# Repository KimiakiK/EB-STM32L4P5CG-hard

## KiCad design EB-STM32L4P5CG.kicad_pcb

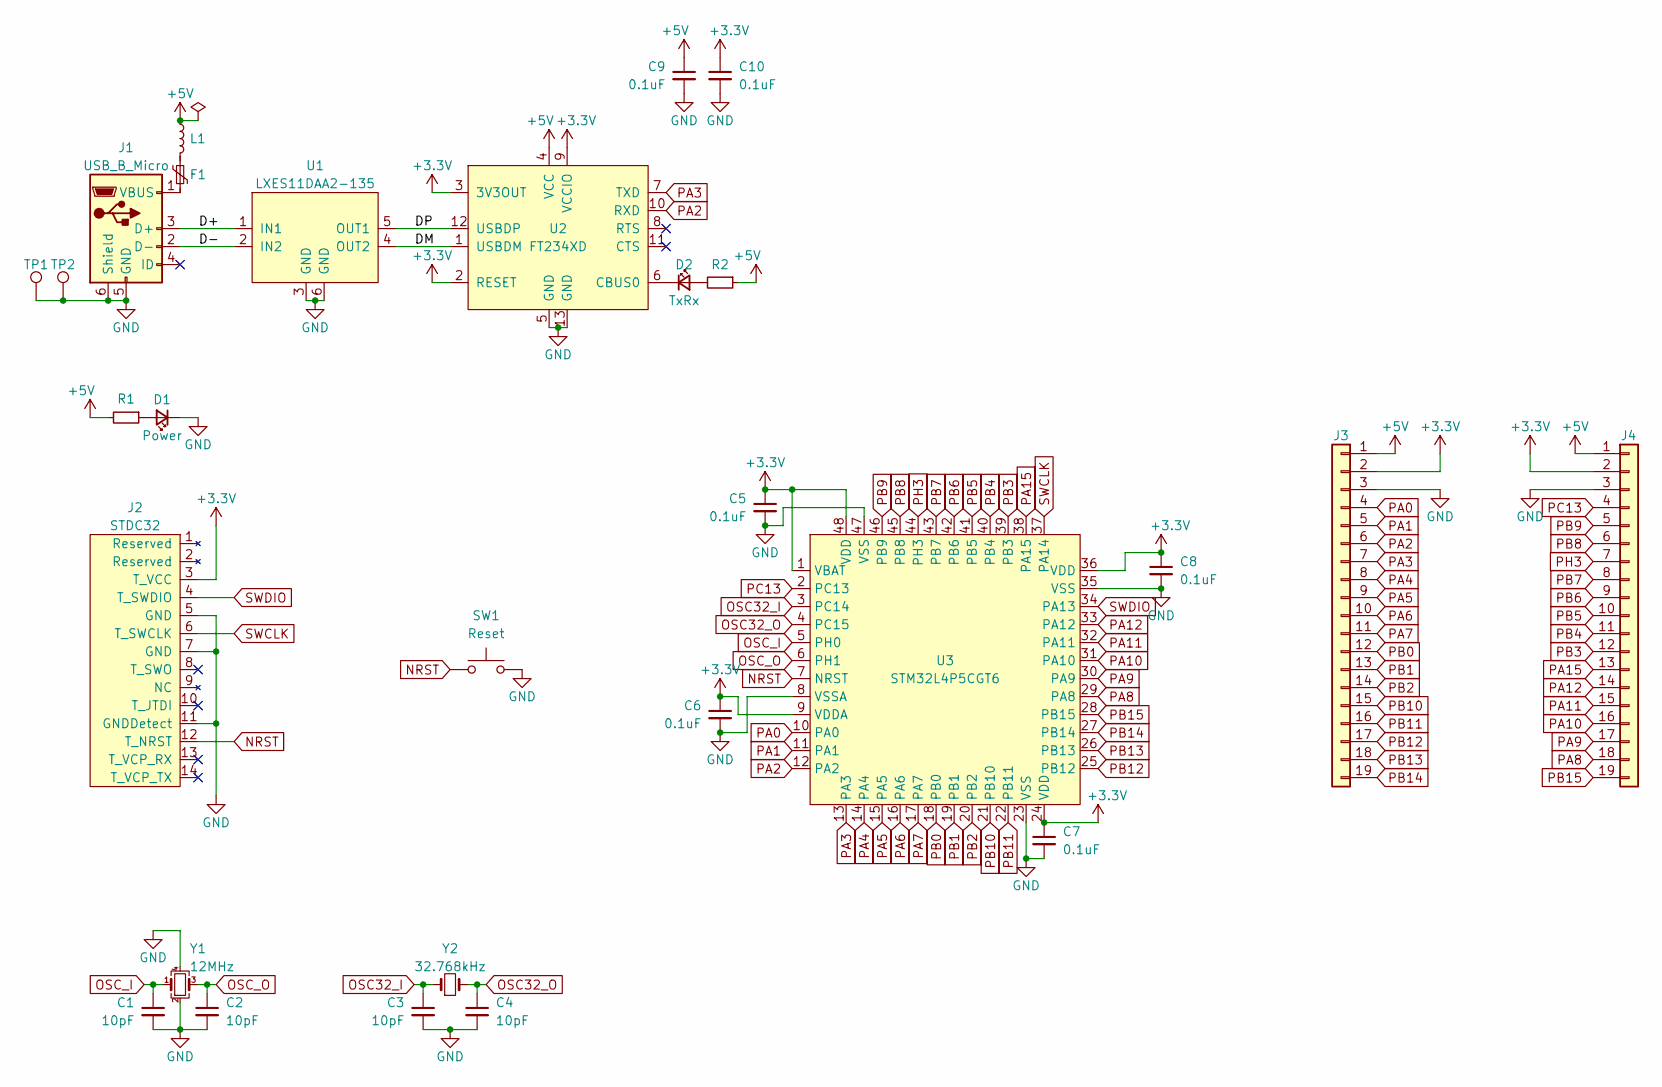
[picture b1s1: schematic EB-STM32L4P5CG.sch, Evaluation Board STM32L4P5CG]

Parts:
C1, C2, C3, C4: 10pF; 1005Metric
C5, C6, C7, C8, C9, C10: 0.1uF; 1608Metric
D1: Power; 1608Metric
D2: TxRx; 1608Metric
F1: ResettableFuse; 1608Metric
J1: USB_B_Micro; ZX62-B-5PA_2
J2: STDC32; BoxHeader_SMD_1.27mm_2x7pin
J3, J4: Conn_01x19; PinHeader_19pin
L1: FerriteBead; 1608Metric
R1, R2: R; 1608Metric
SW1: Reset; SW_TVAF06
TP1, TP2: TestPoint; TestPoint_THTPad_1.6x1.6mm_Drill1.0mm
U1: LXES11DAA2-135; LXES11D
U2: FT234XD; DFN-12-1EP_3x3mm_P0.45mm_EP1.66x2.38mm
U3: STM32L4P5CGT6; LQFP-48_7x7mm_P0.5mm_FusionPCB
Y1: 12MHz; Crystal_SMD_3225-4Pin_3.2x2.5mm_HandSoldering
Y2: 32.768kHz; Crystal_SMD_3215-2Pin

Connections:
+3V3: C5.1, C6.1, C7.1, C8.1, C10.1, J2.3 (T_VCC), J3.2, J4.2, U2.2 (RESET), U2.3 (3V3OUT), U2.9 (VCCIO), U3.1 (VBAT), U3.9 (VDDA), U3.24 (VDD), U3.36 (VDD), U3.48 (VDD)
+5V: C9.1, J3.1, J4.1, L1.1, R1.2, R2.1, U2.4 (VCC)
/D+: J1.3 (D+), U1.1 (IN1)
/D-: J1.2 (D-), U1.2 (IN2)
/DM: U1.4 (OUT2), U2.1 (USBDM)
/DP: U1.5 (OUT1), U2.12 (USBDP)
GND: C1.2, C2.2, C3.2, C4.2, C5.2, C6.2, C7.2, C8.2, C9.2, C10.2, D1.1 (K), J1.5 (GND), J1.6 (Shield), J2.5 (GND), J2.7 (GND), J2.11 (GNDDetect), J3.3, J4.3, SW1.2, TP1.1, TP2.1, U1.3 (GND), U1.6 (GND), U2.5 (GND), U2.13 (GND), U3.8 (VSSA), U3.23 (VSS), U3.35 (VSS), U3.47 (VSS), Y1.2, Y1.4
NRST: J2.12 (T_NRST), SW1.1, U3.7 (NRST)
unnamed: D1.2 (A), R1.1
unnamed: D2.1 (K), U2.6 (CBUS0)
unnamed: D2.2 (A), R2.2
unnamed: F1.1, L1.2
unnamed: F1.2, J1.1 (VBUS)
OSC32_I: C3.1, U3.3 (PC14), Y2.1
OSC32_O: C4.1, U3.4 (PC15), Y2.2
OSC_I: C1.1, U3.5 (PH0), Y1.1
OSC_O: C2.1, U3.6 (PH1), Y1.3
PA0: J3.4, U3.10 (PA0)
PA1: J3.5, U3.11 (PA1)
PA2: J3.6, U2.10 (RXD), U3.12 (PA2)
PA3: J3.7, U2.7 (TXD), U3.13 (PA3)
PA4: J3.8, U3.14 (PA4)
PA5: J3.9, U3.15 (PA5)
PA6: J3.10, U3.16 (PA6)
PA7: J3.11, U3.17 (PA7)
PA8: J4.18, U3.29 (PA8)
PA9: J4.17, U3.30 (PA9)
PA10: J4.16, U3.31 (PA10)
PA11: J4.15, U3.32 (PA11)
PA12: J4.14, U3.33 (PA12)
PA15: J4.13, U3.38 (PA15)
PB0: J3.12, U3.18 (PB0)
PB1: J3.13, U3.19 (PB1)
PB2: J3.14, U3.20 (PB2)
PB3: J4.12, U3.39 (PB3)
PB4: J4.11, U3.40 (PB4)
PB5: J4.10, U3.41 (PB5)
PB6: J4.9, U3.42 (PB6)
PB7: J4.8, U3.43 (PB7)
PB8: J4.6, U3.45 (PB8)
PB9: J4.5, U3.46 (PB9)
PB10: J3.15, U3.21 (PB10)
PB11: J3.16, U3.22 (PB11)
PB12: J3.17, U3.25 (PB12)
PB13: J3.18, U3.26 (PB13)
PB14: J3.19, U3.27 (PB14)
PB15: J4.19, U3.28 (PB15)
PC13: J4.4, U3.2 (PC13)
PH3: J4.7, U3.44 (PH3)
SWCLK: J2.6 (T_SWCLK), U3.37 (PA14)
SWDIO: J2.4 (T_SWDIO), U3.34 (PA13)

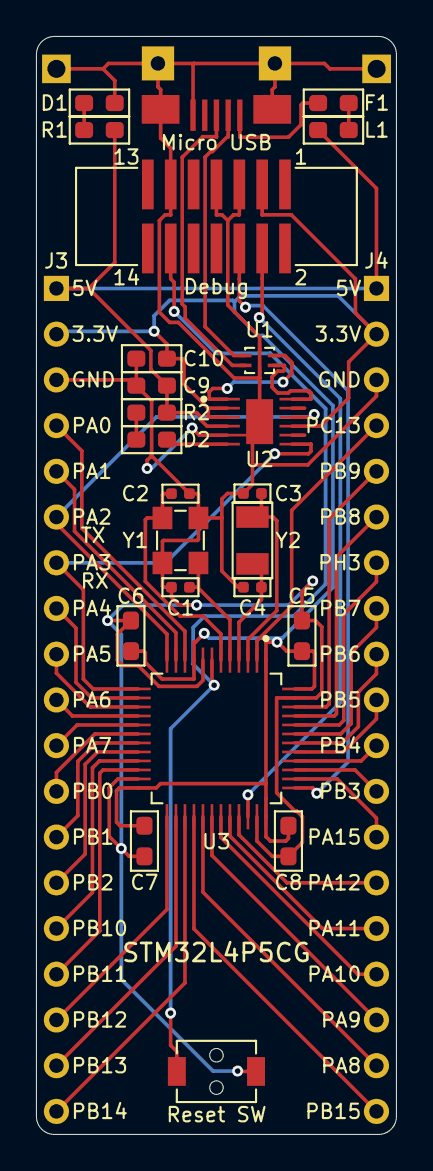
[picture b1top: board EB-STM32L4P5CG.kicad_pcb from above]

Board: 2 copper layers, 20.0 x 61.0 mm, 28 parts (0 on the bottom side), 51 nets.

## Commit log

2021-07-10 基板 V1.0
